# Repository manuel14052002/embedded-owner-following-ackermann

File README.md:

# A2R-bot

A small RC car that follows its owner around.

I built this on top of a 1:10 Ackermann RC chassis. You raise your hand in front of it, it learns what you look like, and from then on it follows you at a couple of metres, indoors or outside, while trying not to hit anything (or anyone) on the way. It ignores other people, and if it loses you for a moment it keeps track of where you probably are using the lidar until the camera finds you again.

The person-recognition part started from [FollowMe](https://arxiv.org/abs/2311.12992) (Rollo et al.), which I adapted to run on a Jetson and extended in two ways:

- **multi-view re-identification**: instead of one "average" picture of the owner, the robot keeps many separate views (front, back, side, near, far) and compares new detections against the closest ones;
- **lidar owner keeping**: a 2D lidar tracker that holds on to the owner when the camera loses them, which happens a lot on a car that can't turn on the spot.

This was my student research project (TDK) and Thesis work at the University of Debrecen, Faculty of Engineering, in 2026.

## In action

These are screen recordings of the robot's debug view, sped up 2.5×. The green outline is the person it thinks is its owner; the small panel at the bottom right is the lidar view from above (yellow dot = owner, cross = current goal).

**Enrolling and following down a corridor.** The yellow box is the "learning you" phase; once it turns green it starts following.

**Following outdoors.** Low sun and backlight, which is about the hardest light for the camera.

**Turning away.** When the individual walk off to the side the car can't turn on the spot, so it plans a manoeuvre to get me back in view.

## What's in the repo

```
robot_ws/              ROS 2 workspace that runs on the Raspberry Pi 4
  src/a2r_bot_follow/      owner fusion, Kalman filter, follow manager, local planner,
                           collision monitor, command mux
  src/a2r_bot_arduino/     serial bridge + ESP32 firmware (servo, ESC, IMU, battery)
  src/a2r_bot_description/ URDF model
  src/a2r_bot_info/docs/   older notes: architecture, topics, kinematics, wiring, testing
jetson_owner_tracker/  perception on the Jetson (FollowMe adaptation, re-ID, gestures,
                       lidar owner keeper, ROS 2 nodes in ros2/followme_ros)
robot_face/            the little face shown on the robot's display
hardware/              KiCad project of the carrier board + schematic / PCB renders
tools/simulation/      MATLAB / Python simulation of the follow controller
legacy_ros2_ws/        my first prototype (simple human tracker), kept for reference
```

## How it works (short version)

```
 RealSense D435 ──► Jetson: segment people ─► re-ID ─► "is this my owner?" ─► owner position
                                                                │
 RPLIDAR A2M12 ───► Jetson: lidar owner keeper ◄────────────────┘ (camera picks the track)
                                │
                                ▼
                    Raspberry Pi 4: owner fusion ─► Kalman filter ─► goal 1.6 m behind owner
                                                     ─► local planner ─► collision monitor
                                │
                                ▼  JSON over serial
                    Arduino Nano ESP32 ─► PCA9685 ─► steering servo + ESC
```

The Jetson does everything that needs a GPU: person segmentation (YOLO11n-seg), appearance embeddings (OSNet), deciding which person is the owner, and hand gestures. It also runs the lidar keeper, because the keeper and the camera have to talk to each other constantly. The Raspberry Pi does the "driving" part: it fuses the owner position, filters it, picks a goal point and plans a path that the Ackermann steering can actually follow. The ESP32 only turns speed and steering commands into PWM and has a watchdog that stops the car if commands stop arriving.

The longer explanation, including how enrolment, the re-ID decision and the lidar keeper work, is in [docs/how-it-works.md](docs/how-it-works.md). Parts and wiring are in [docs/hardware.md](docs/hardware.md).

## Running it

You need ROS 2 (I used Humble) on both the Pi and the Jetson, on the same network.

**Raspberry Pi**

```bash
cd robot_ws
colcon build --symlink-install
source install/setup.bash
ros2 launch a2r_bot_follow follow.launch.py
```

**Jetson**

The model files are not in the repo (too big). Export YOLO11n-seg and OSNet x1_0 to TensorRT on the Jetson first; the steps are in [jetson_owner_tracker/README_FOLLOWME.md](jetson_owner_tracker/README_FOLLOWME.md). Then:

```bash
cd jetson_owner_tracker
pip install -r requirements.txt
# build the ROS 2 package in ros2/followme_ros, then:
ros2 launch followme_ros followme.launch.py
```

**ESP32 firmware**

Open `robot_ws/src/a2r_bot_arduino/firmware/a2r_bot_firmware/` in the Arduino IDE (board: Arduino Nano ESP32) and flash it. The serial protocol is described in [SERIAL_PROTOCOL.md](robot_ws/src/a2r_bot_info/docs/SERIAL_PROTOCOL.md).

**Using the robot**

1. Stand alone in front of the camera, about 2 m away, and hold up an open hand for a second or two.
2. Stay in view while it learns you (about 12 seconds). Turning around slowly helps.
3. Make a fist to start following, show a low open palm to make it wait. Hold your hand up for 3 s to release it.

The more detailed bring-up checklist is in [QUICKSTART.md](robot_ws/src/a2r_bot_info/docs/QUICKSTART.md), and [TROUBLESHOOTING.md](robot_ws/src/a2r_bot_info/docs/TROUBLESHOOTING.md) has the problems I ran into.

## Configuration

Most parameters live in `robot_ws/src/a2r_bot_follow/config/params.yaml` (follow distance, planner choice, speed limits, collision zones) and `jetson_owner_tracker/config/followme_deploy.yaml` (detection, re-ID and enrolment settings).

The GPS fallback uses a SIM7600 modem and reads the owner's phone position from a Firebase database. I removed my own database URL and SIM PIN from the code, so set `firebase_url` and `sim_pin` in `params.yaml` yourself if you want that feature, and don't commit them.

## Known issues / TODO

- When it loses you, it searches by turning in place, which is not great for a car. It should drive towards the last place it saw you.
- Recognition gets unreliable when you are further than ~3.5 m away or very close (only legs in view).
- Enrolment can lock onto the wrong person if someone else is in view at the same time. Do it alone for now.
- There are no wheel encoders, so speed control is open loop.
- The carrier board mixes 3.3 V and 5 V I²C pull-ups and powers the ESP32 only from USB. That probably explains the occasional "PCA9685 not responding" and serial reconnects; it's on the list for the next board revision.
- The lidar keeper's leg-shape identity model (`leg_signature.py`) only runs in logging mode so far.

## Credits

- FollowMe: F. Rollo, A. Zunino, G. Raiola, F. Amadio, A. Ajoudani, N. Tsagarakis, *FollowMe: a robust person following framework based on visual re-identification and gestures*, arXiv:2311.12992.
- OSNet (K. Zhou et al.), YOLO11 (Ultralytics), MediaPipe Hands, ROS 2, Slamtec sllidar_ros2, Intel RealSense SDK.
Authors: Manuel Afonso Fernandes Junior and David Mbomko Pani
  -Linkedin: @manuel-jr

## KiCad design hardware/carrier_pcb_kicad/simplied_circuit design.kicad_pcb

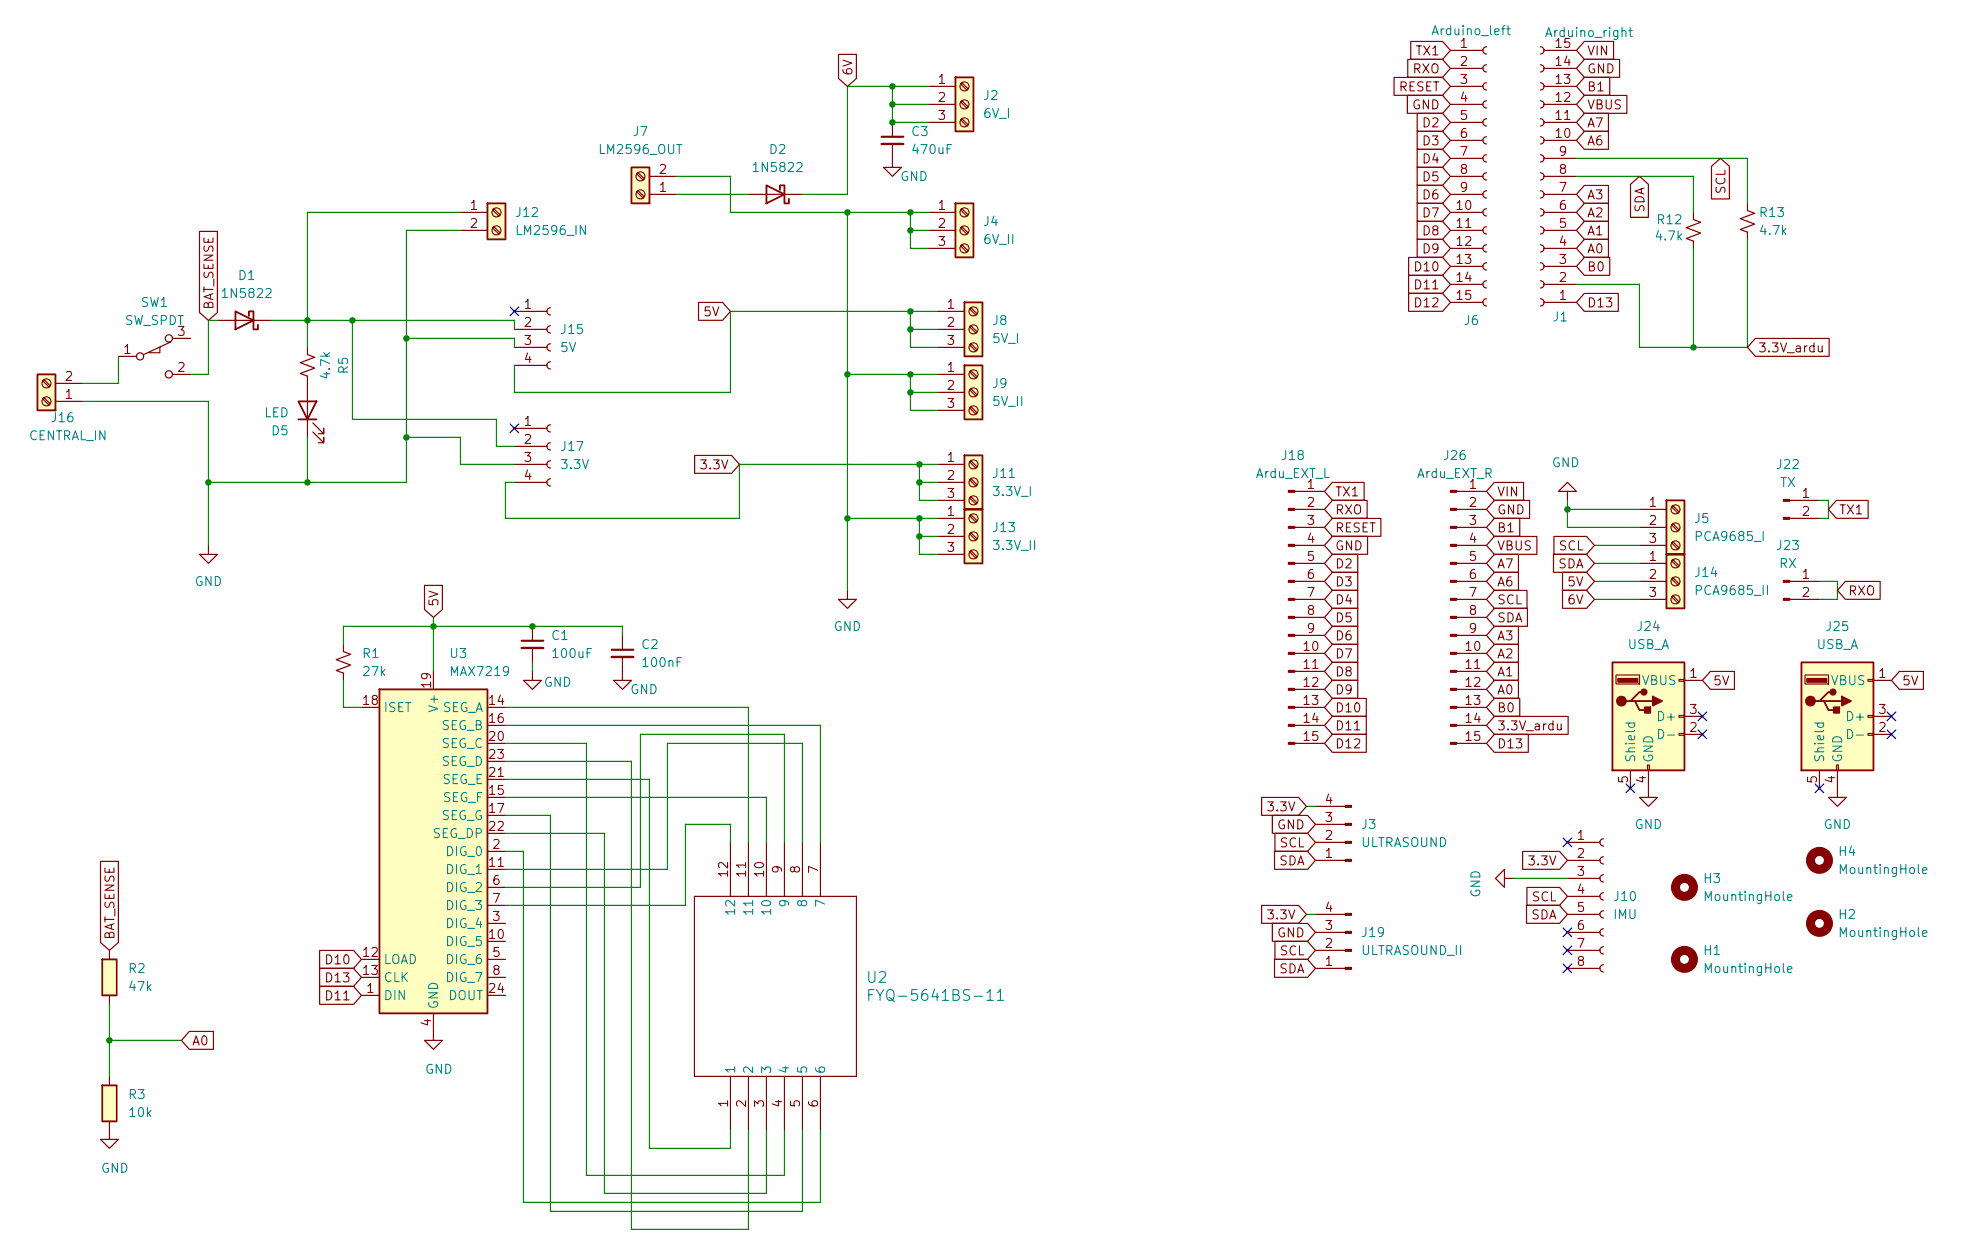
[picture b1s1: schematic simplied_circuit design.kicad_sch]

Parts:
C1: 100uF; C_Radial_D5.0mm_H7.0mm_P2.00mm
C2: 100nF; C_Disc_D5.0mm_W2.5mm_P2.50mm
C3: 470uF; CP_Radial_D10.0mm_P5.00mm
D1, D2: 1N5822; D_DO-201AD_P15.24mm_Horizontal
D5: LED; LED_D4.0mm
H1, H2, H3, H4: MountingHole; MountingHole_3mm
J1: Arduino_right; PinSocket_1x15_P2.54mm_Vertical
J2: 6V_I; TerminalBlock_Phoenix_MKDS-1-3-3.81_1x03_P3.81mm_Horizontal
J3: ULTRASOUND; PinHeader_1x04_P2.54mm_Vertical
J4: 6V_II; TerminalBlock_Phoenix_MKDS-1-3-3.81_1x03_P3.81mm_Horizontal
J5: PCA9685_I; TerminalBlock_Phoenix_MKDS-1-3-3.81_1x03_P3.81mm_Horizontal
J6: Arduino_left; PinSocket_1x15_P2.54mm_Vertical
J7: LM2596_OUT; TerminalBlock_Phoenix_MKDS-1-2-3.81_1x02_P3.81mm_Horizontal
J8: 5V_I; TerminalBlock_Phoenix_MKDS-1-3-3.81_1x03_P3.81mm_Horizontal
J9: 5V_II; TerminalBlock_Phoenix_MKDS-1-3-3.81_1x03_P3.81mm_Horizontal
J10: IMU; PinSocket_1x08_P2.54mm_Vertical
J11: 3.3V_I; TerminalBlock_Phoenix_MKDS-1-3-3.81_1x03_P3.81mm_Horizontal
J12: LM2596_IN; TerminalBlock_Phoenix_MKDS-1-2-3.81_1x02_P3.81mm_Horizontal
J13: 3.3V_II; TerminalBlock_Phoenix_MKDS-1-3-3.81_1x03_P3.81mm_Horizontal
J14: PCA9685_II; TerminalBlock_Phoenix_MKDS-1-3-3.81_1x03_P3.81mm_Horizontal
J15: 5V; PinSocket_1x04_P2.54mm_Vertical
J16: CENTRAL_IN; TerminalBlock_Phoenix_MKDS-3-2-5.08_1x02_P5.08mm_Horizontal
J17: 3.3V; PinSocket_1x04_P2.54mm_Vertical
J18: Ardu_EXT_L; PinSocket_1x15_P2.54mm_Vertical
J19: ULTRASOUND_II; PinHeader_1x04_P2.54mm_Vertical
J22: TX; PinHeader_1x02_P2.54mm_Vertical
J23: RX; PinHeader_1x02_P2.54mm_Vertical
J24, J25: USB_A; USB_A_Connfly_DS1095
J26: Ardu_EXT_R; PinSocket_1x15_P2.54mm_Vertical
R1: 27k; R_Axial_DIN0207_L6.3mm_D2.5mm_P10.16mm_Horizontal
R2: 47k; R_Axial_DIN0207_L6.3mm_D2.5mm_P10.16mm_Horizontal
R3: 10k; R_Axial_DIN0207_L6.3mm_D2.5mm_P10.16mm_Horizontal
R5, R12, R13: 4.7k; R_Axial_DIN0207_L6.3mm_D2.5mm_P10.16mm_Horizontal
SW1: SW_SPDT; SW_Toggle_Blue_wSlots
U2: FYQ-5641BS-11; IC12_FYQ-5641BS-11_FOY
U3: MAX7219; DIP-24_W7.62mm_Socket

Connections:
3.3V: J3.4, J10.2, J11.1, J11.2, J11.3, J17.4, J19.4
3.3V_ardu: J1.2, J26.14, R12.2, R13.2
5V: C1.1, C2.1, J8.1, J8.2, J8.3, J14.2, J15.4, J24.1 (VBUS), J25.1 (VBUS), R1.2, U3.19 (V+)
6V: C3.1, D2.1 (K), J2.1, J2.2, J2.3, J14.3
A0: J1.4, J26.12, R2.2, R3.1
A1: J1.5, J26.11
A2: J1.6, J26.10
A3: J1.7, J26.9
A6: J1.10, J26.6
A7: J1.11, J26.5
B0: J1.3, J26.13
B1: J1.13, J26.3
BAT_SENSE: D1.2 (A), R2.1, SW1.2 (B)
D2: J6.5, J18.5
D3: J6.6, J18.6
D4: J6.7, J18.7
D5: J6.8, J18.8
D6: J6.9, J18.9
D7: J6.10, J18.10
D8: J6.11, J18.11
D9: J6.12, J18.12
D10: J6.13, J18.13, U3.12 (LOAD)
D11: J6.14, J18.14, U3.1 (DIN)
D12: J6.15, J18.15
D13: J1.1, J26.15, U3.13 (CLK)
GND: C1.2, C2.2, C3.2, D5.1 (K), J1.14, J3.3, J4.1, J4.2, J4.3, J5.1, J5.2, J6.4, J7.2, J9.1, J9.2, J9.3, J10.3, J12.2, J13.1, J13.2, J13.3, J15.3, J16.1, J17.3, J18.4, J19.3, J24.4 (GND), J25.4 (GND), J26.2, R3.2, U3.4 (GND), U3.9 (GND)
unnamed: D1.1 (K), J12.1, J15.2, J17.2, R5.1
unnamed: D2.2 (A), J7.1
unnamed: D5.2 (A), R5.2
unnamed: J16.2, SW1.1 (A)
unnamed: U2.6, U3.2 (DIG_0)
unnamed: U2.8, U3.11 (DIG_1)
unnamed: U2.9, U3.6 (DIG_2)
unnamed: U2.12, U3.7 (DIG_3)
unnamed: R1.1, U3.18 (ISET)
unnamed: U2.11, U3.14 (SEG_A)
unnamed: U2.7, U3.16 (SEG_B)
unnamed: U2.4, U3.20 (SEG_C)
unnamed: U2.2, U3.23 (SEG_D)
unnamed: U2.3, U3.22 (SEG_DP)
unnamed: U2.1, U3.21 (SEG_E)
unnamed: U2.10, U3.15 (SEG_F)
unnamed: U2.5, U3.17 (SEG_G)
RESET: J6.3, J18.3
RXO: J6.2, J18.2, J23.1, J23.2
SCL: J1.9, J3.2, J5.3, J10.4, J19.2, J26.7, R13.1
SDA: J1.8, J3.1, J10.5, J14.1, J19.1, J26.8, R12.1
TX1: J6.1, J18.1, J22.1, J22.2
VBUS: J1.12, J26.4
VIN: J1.15, J26.1

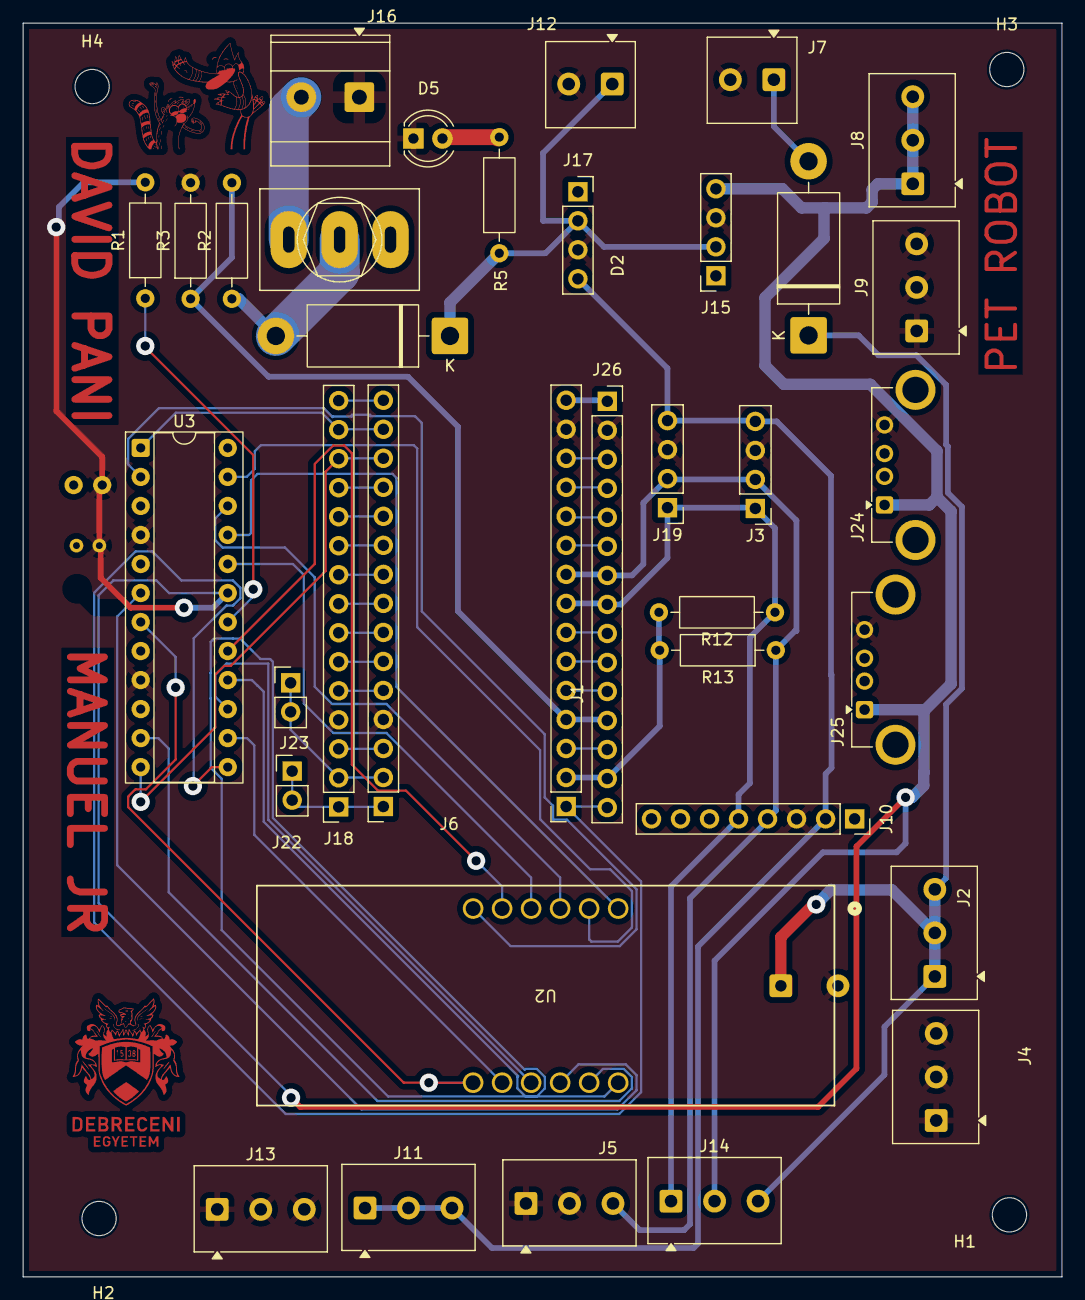
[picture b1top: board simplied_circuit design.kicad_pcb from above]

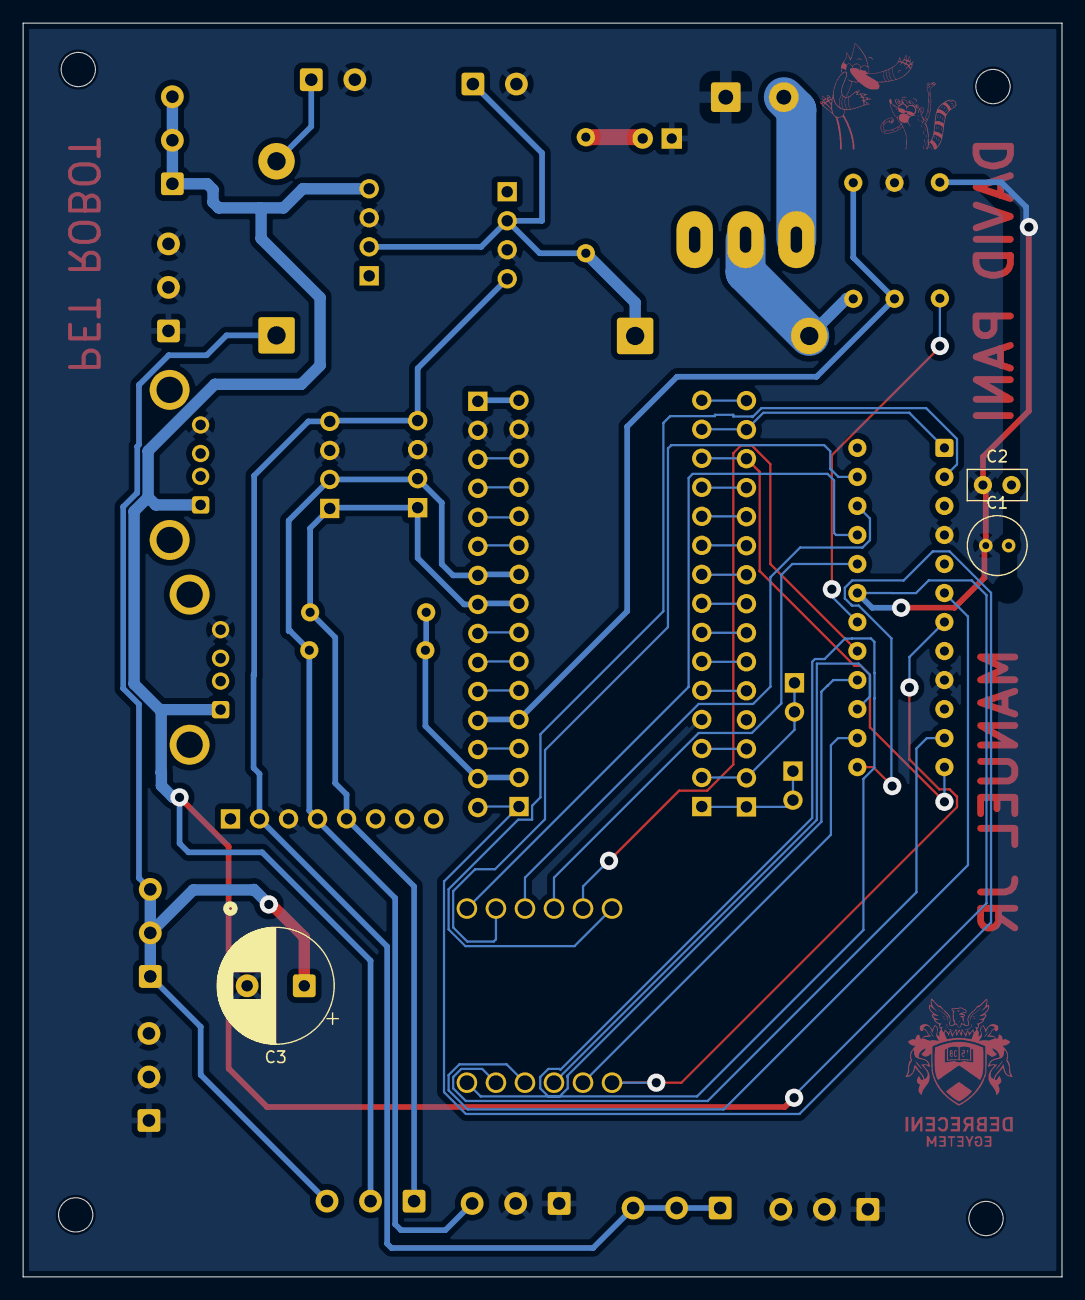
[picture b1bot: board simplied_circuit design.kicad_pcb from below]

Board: 2 copper layers, 90.9 x 109.7 mm, 43 parts (3 on the bottom side), 50 nets.
